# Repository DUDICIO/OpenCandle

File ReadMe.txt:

Open Candle Project

Smart desk lamp project

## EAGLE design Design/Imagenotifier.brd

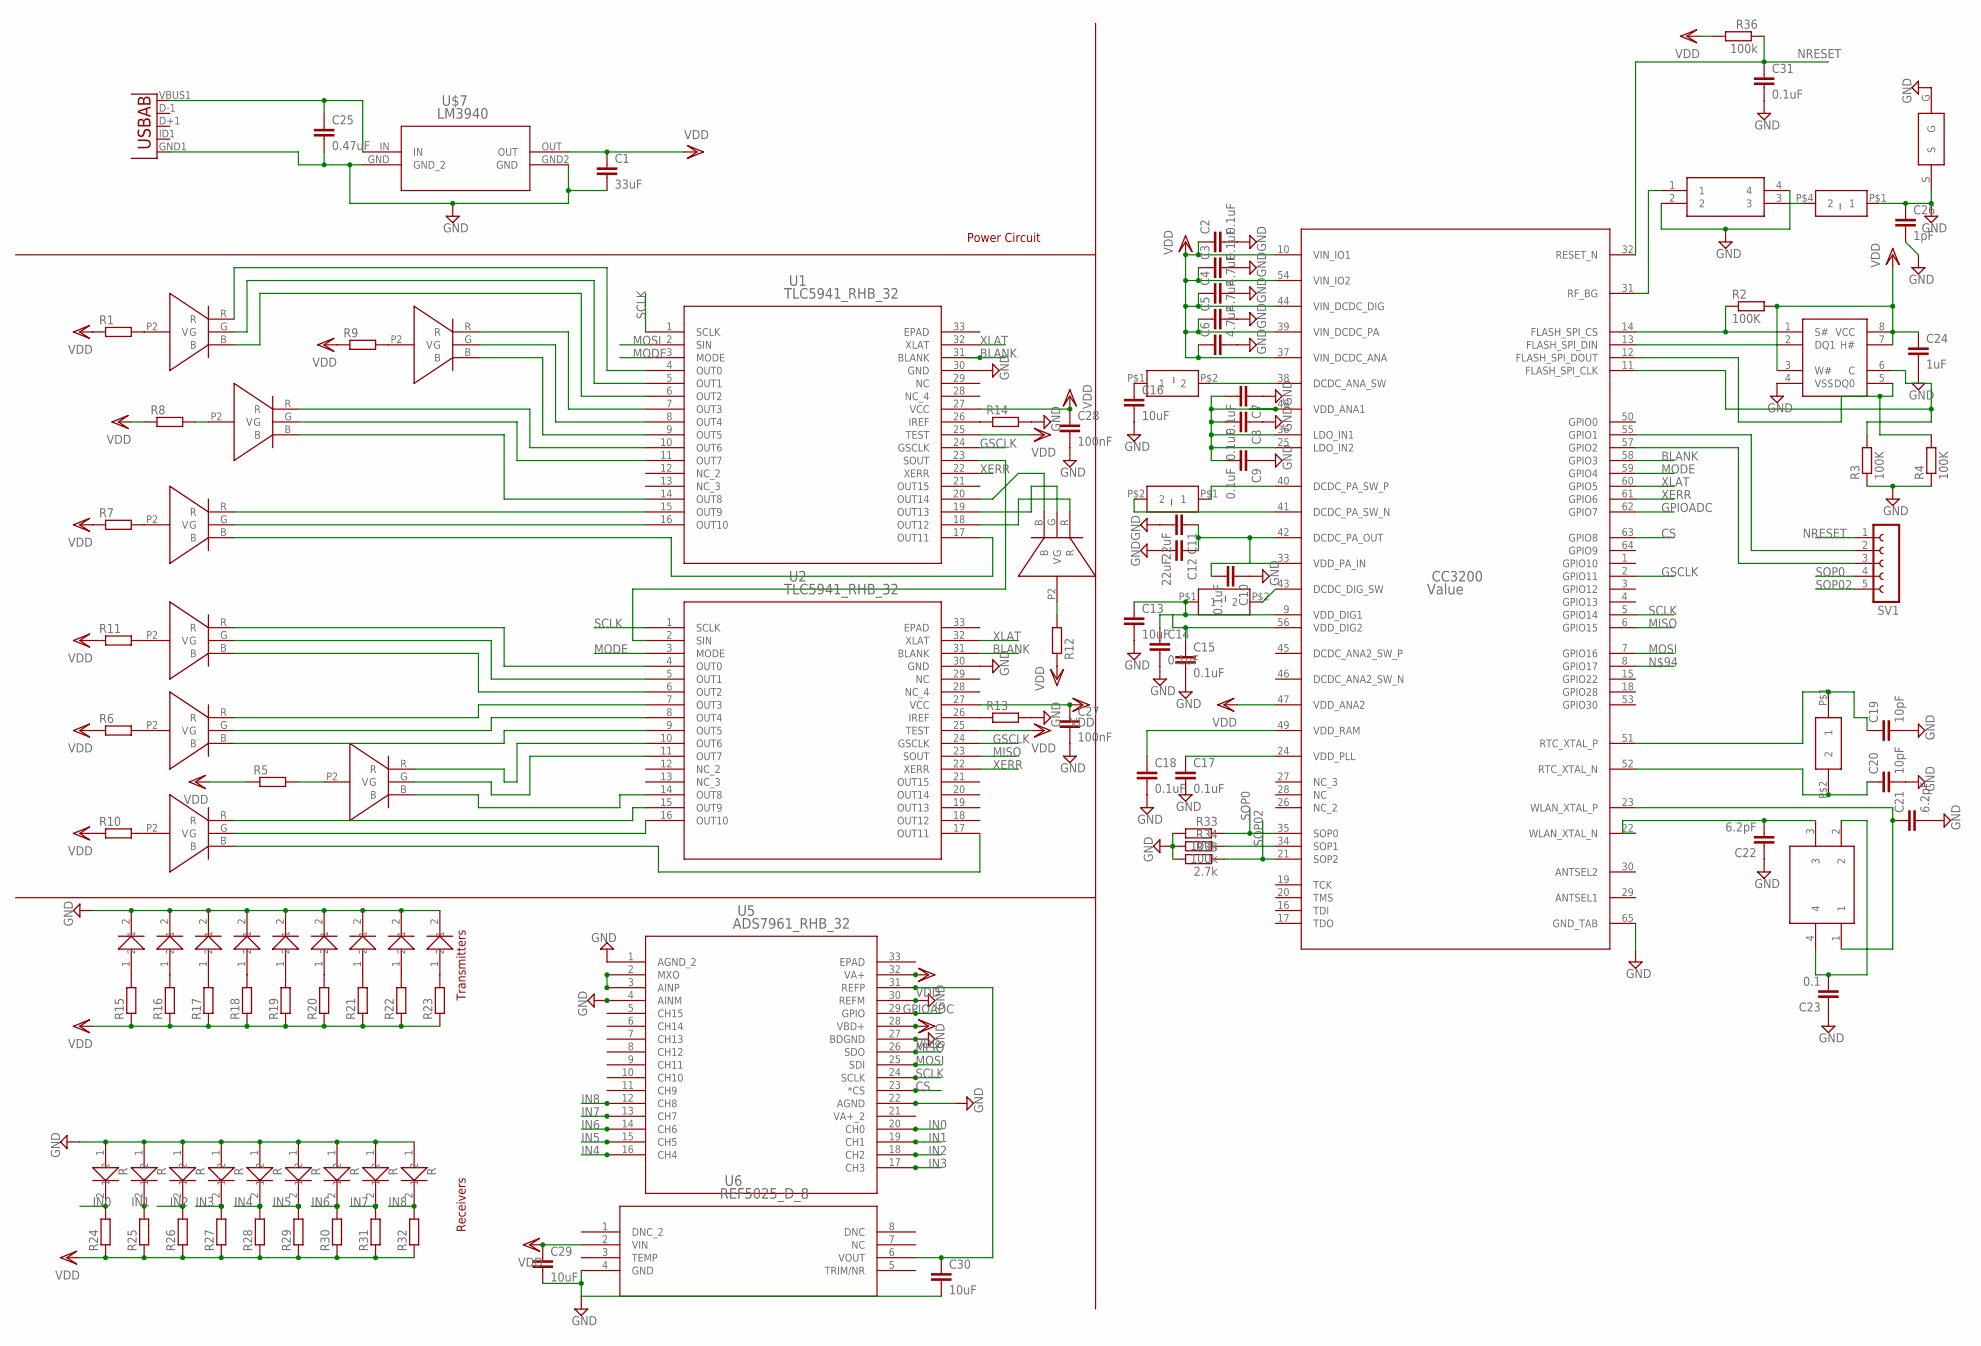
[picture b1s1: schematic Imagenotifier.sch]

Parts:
1: IRTRANS; IRTRANSCIEVER
C1: 33uF; C1206
C2, C3, C7, C8, C9, C10, C14, C15, C17, C18, C31: 0.1uF; 0805
C4, C5, C6: 4.7uF; 0805
C11, C12: 22uF; 0805
C13, C16, C29, C30: 10uF; 0805
C19, C20: 10pF; 0805
C21, C22: 6.2pF; 0805
C23: 0.1; 0805
C24: 1uF; 0805
C25: 0.47uF; C0805
C26: 1pF; 0805
C27, C28: 100nF; 0805
CC3200: Value; RGC0064A
CRYSTAL: ABS07-32.768KHZ-T
R1, R5, R6, R7, R8, R9, R10, R11, R12, R13, R14, R15, R16, R17, R18, R19, R20, R21, R22, R23, R24, R25, R26, R27, R28, R29, R30, R31, R32: R; R0805
R2, R3, R4: 100K; R0805
R33, R34, R36: 100k; R0805
R35: 2.7k; R0805
SV1: FE05-1
U1, U2: TLC5941_RHB_32; RHB32_3P15X3P15
U3: USB""; USB-MICRO-SMD
U5: ADS7961_RHB_32; RHB32_2P7X2P7
U6: REF5025_D_8; D8
U$1: IND1UH1008P; 1008IND2.2UH
U$2, U$3: IND2.6UH1008P; 1008IND2.2UH
U$5: Q24FA20H00396
U$6: FLASHM25PX80; SO08
U$7: LM3940; MP04A
U$8: DEA202450BT-1294C1-H
U$9: IND3.6NH402P; 0402INDUCTOR3.6NH
U$10: ANTENNAE-AH316M245001-T; ANTENNA-AH316M245001-T
U$11, U$12, U$13, U$14, U$15, U$16, U$17, U$18, U$19: RGBLED; 0.25WATT_RGB_THROUGH
U$20, U$22, U$23, U$24, U$25, U$26, U$27, U$28: IRTRANS; IRTRANSCIEVER
U$29, U$31, U$33, U$35, U$37, U$39, U$41, U$43, U$44: IRREC; IRREIVER

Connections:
BLANK: CC3200.58 (GPIO3), U1.31 (BLANK), U2.31 (BLANK)
CS: CC3200.63 (GPIO8), U5.23 (*CS)
EPAD: U5.33 (EPAD)
GND: 1.2, C1.2, C2.2, C3.2, C4.2, C5.2, C6.2, C7.1, C8.1, C9.1, C10.1, C11.2, C12.2, C13.2, C14.2, C15.2, C16.2, C18.2, C19.2, C20.2, C21.2, C22.1, C23.1, C24.2, C25.2, C26.1, C26.2, C27.2, C28.2, C29.2, C30.2, C31.2, CC3200.65 (GND_TAB), R3.1, R4.1, R13.2, R14.2, R33.2, R34.2, R35.2, U1.30 (GND), U2.30 (GND), U3.GND1 (GND), U5.4 (AINM), U5.22 (AGND), U5.27 (BDGND), U5.30 (REFM), U6.4 (GND), U$6.4 (VSS), U$7.GND (GND_2), U$7.GND2 (GND), U$8.2, U$8.4, U$9.P$1 (1), U$10.G, U$10.S, U$20.2, U$22.2, U$23.2, U$24.2, U$25.2, U$26.2, U$27.2, U$28.2, U$29.1, U$31.1, U$33.1, U$35.1, U$37.1, U$39.1, U$41.1, U$43.1, U$44.1
GPIOADC: CC3200.62 (GPIO7), U5.29 (GPIO)
GSCLK: CC3200.2 (GPIO11), U1.24 (GSCLK), U2.24 (GSCLK)
IN0: R24.2, U5.20 (CH0), U$29.2
IN1: R25.2, U5.19 (CH1), U$31.2
IN2: R26.2, U5.18 (CH2), U$33.2
IN3: R27.2, U5.17 (CH3), U$35.2
IN4: R28.2, U5.16 (CH4), U$37.2
IN5: R29.2, U5.15 (CH5), U$39.2
IN6: R30.2, U5.14 (CH6), U$41.2
IN7: R31.2, U5.13 (CH7), U$43.2
IN8: R32.2, U5.12 (CH8), U$44.2
MISO: CC3200.6 (GPIO15), U2.23 (SOUT), U5.26 (SDO)
MODE: CC3200.59 (GPIO4), U1.3 (MODE), U2.3 (MODE)
MOSI: CC3200.7 (GPIO16), U1.2 (SIN), U5.25 (SDI)
unnamed: C7.2, C8.2, C9.2, CC3200.25 (LDO_IN2), CC3200.36 (LDO_IN1), CC3200.48 (VDD_ANA1)
unnamed: CC3200.40 (DCDC_PA_SW_P), U$1.P$1 (1)
unnamed: CC3200.41 (DCDC_PA_SW_N), U$1.P$2 (2)
unnamed: C10.2, C11.1, C12.1, CC3200.33 (VDD_PA_IN), CC3200.42 (DCDC_PA_OUT)
unnamed: C13.1, C14.1, CC3200.9 (VDD_DIG1), U$3.P$1 (1)
unnamed: CC3200.43 (DCDC_DIG_SW), U$3.P$2 (2)
unnamed: C15.1, CC3200.56 (VDD_DIG2)
unnamed: CC3200.38 (DCDC_ANA_SW), U$2.P$2 (2)
unnamed: C16.1, U$2.P$1 (1)
unnamed: C18.1, CC3200.49 (VDD_RAM)
unnamed: C17.1, CC3200.24 (VDD_PLL)
unnamed: C19.1, CC3200.51 (RTC_XTAL_P), CRYSTAL.P$1 (1)
unnamed: C20.1, CC3200.52 (RTC_XTAL_N), CRYSTAL.P$2 (2)
unnamed: C21.1, CC3200.23 (WLAN_XTAL_P), U$5.1
unnamed: C22.2, CC3200.22 (WLAN_XTAL_N), U$5.3
unnamed: C23.2, U$5.2, U$5.4
unnamed: CC3200.14 (FLASH_SPI_CS), R2.1, U$6.1 (S#)
unnamed: CC3200.13 (FLASH_SPI_DIN), U$6.2 (DQ1)
unnamed: CC3200.11 (FLASH_SPI_CLK), R3.2, U$6.6 (C)
unnamed: C25.1, U3.VBUS1 (VBUS), U$7.IN
unnamed: CC3200.31 (RF_BG), U$8.1
unnamed: U$8.3, U$9.P$4 (2)
unnamed: R1.2, U$11.P2 (V)
unnamed: R5.2, U$14.P2 (V)
unnamed: R6.2, U$17.P2 (V)
unnamed: R7.2, U$12.P2 (V)
unnamed: R8.2, U$18.P2 (V)
unnamed: R9.2, U$15.P2 (V)
unnamed: R10.2, U$19.P2 (V)
unnamed: R11.2, U$16.P2 (V)
unnamed: R12.2, U$13.P2 (V)
unnamed: U1.4 (OUT0), U$11.R
unnamed: U1.5 (OUT1), U$11.G
unnamed: U1.6 (OUT2), U$11.B
unnamed: U1.7 (OUT3), U$15.R
unnamed: U1.8 (OUT4), U$15.G
unnamed: U1.9 (OUT5), U$15.B
unnamed: U1.10 (OUT6), U$18.R
unnamed: U1.11 (OUT7), U$18.G
unnamed: U1.14 (OUT8), U$18.B
unnamed: U1.15 (OUT9), U$12.R
unnamed: U1.16 (OUT10), U$12.G
unnamed: U1.17 (OUT11), U$12.B
unnamed: U1.18 (OUT12), U$13.R
unnamed: U1.19 (OUT13), U$13.G
unnamed: U1.20 (OUT14), U$13.B
unnamed: U2.4 (OUT0), U$16.R
unnamed: U2.5 (OUT1), U$16.G
unnamed: U2.6 (OUT2), U$16.B
unnamed: U2.7 (OUT3), U$17.R
unnamed: U2.9 (OUT5), U$17.B
unnamed: U2.10 (OUT6), U$14.R
unnamed: U2.8 (OUT4), U$17.G
unnamed: U2.11 (OUT7), U$14.G
unnamed: U2.14 (OUT8), U$14.B
unnamed: U5.2 (MXO), U5.3 (AINP)
unnamed: U2.15 (OUT9), U$19.R
unnamed: U2.16 (OUT10), U$19.G
unnamed: U2.17 (OUT11), U$19.B
unnamed: U1.23 (SOUT), U2.2 (SIN)
unnamed: 1.1, R15.2
unnamed: R14.1, U1.26 (IREF)
unnamed: R16.2, U$22.1
unnamed: R13.1, U2.26 (IREF)
unnamed: C30.1, U5.31 (REFP), U6.6 (VOUT)
unnamed: CC3200.34 (SOP1), R34.1
unnamed: CC3200.55 (GPIO1), SV1.2
unnamed: CC3200.57 (GPIO2), SV1.3
unnamed: R17.2, U$23.1
unnamed: R18.2, U$24.1
unnamed: R19.2, U$25.1
unnamed: R20.2, U$26.1
unnamed: R21.2, U$27.1
unnamed: R22.2, U$28.1
unnamed: R23.2, U$20.1
unnamed: CC3200.12 (FLASH_SPI_DOUT), R4.2, U$6.5 (DQ0)
NRESET: C31.1, CC3200.32 (RESET_N), R36.1, SV1.1
SCLK: CC3200.5 (GPIO14), U1.1 (SCLK), U2.1 (SCLK), U5.24 (SCLK)
SOP0: CC3200.35 (SOP0), R33.1, SV1.4
SOP02: CC3200.21 (SOP2), R35.1, SV1.5
VA+_2: U5.21 (VA+_2)
VDD: C1.1, C2.1, C3.1, C4.1, C5.1, C6.1, C24.1, C27.1, C28.1, C29.1, CC3200.10 (VIN_IO1), CC3200.37 (VIN_DCDC_ANA), CC3200.39 (VIN_DCDC_PA), CC3200.44 (VIN_DCDC_DIG), CC3200.47 (VDD_ANA2), CC3200.54 (VIN_IO2), R1.1, R2.2, R5.1, R6.1, R7.1, R8.1, R9.1, R10.1, R11.1, R12.1, R15.1, R16.1, R17.1, R18.1, R19.1, R20.1, R21.1, R22.1, R23.1, R24.1, R25.1, R26.1, R27.1, R28.1, R29.1, R30.1, R31.1, R32.1, R36.2, U1.25 (TEST), U1.27 (VCC), U2.25 (TEST), U2.27 (VCC), U5.28 (VBD+), U5.32 (VA+), U6.2 (VIN), U$6.3 (W#), U$6.7 (H#), U$6.8 (VCC), U$7.OUT
XERR: CC3200.61 (GPIO6), U1.22 (XERR), U2.22 (XERR)
XLAT: CC3200.60 (GPIO5), U1.32 (XLAT), U2.32 (XLAT)

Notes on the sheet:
Power Circuit
Transmitters
Receivers

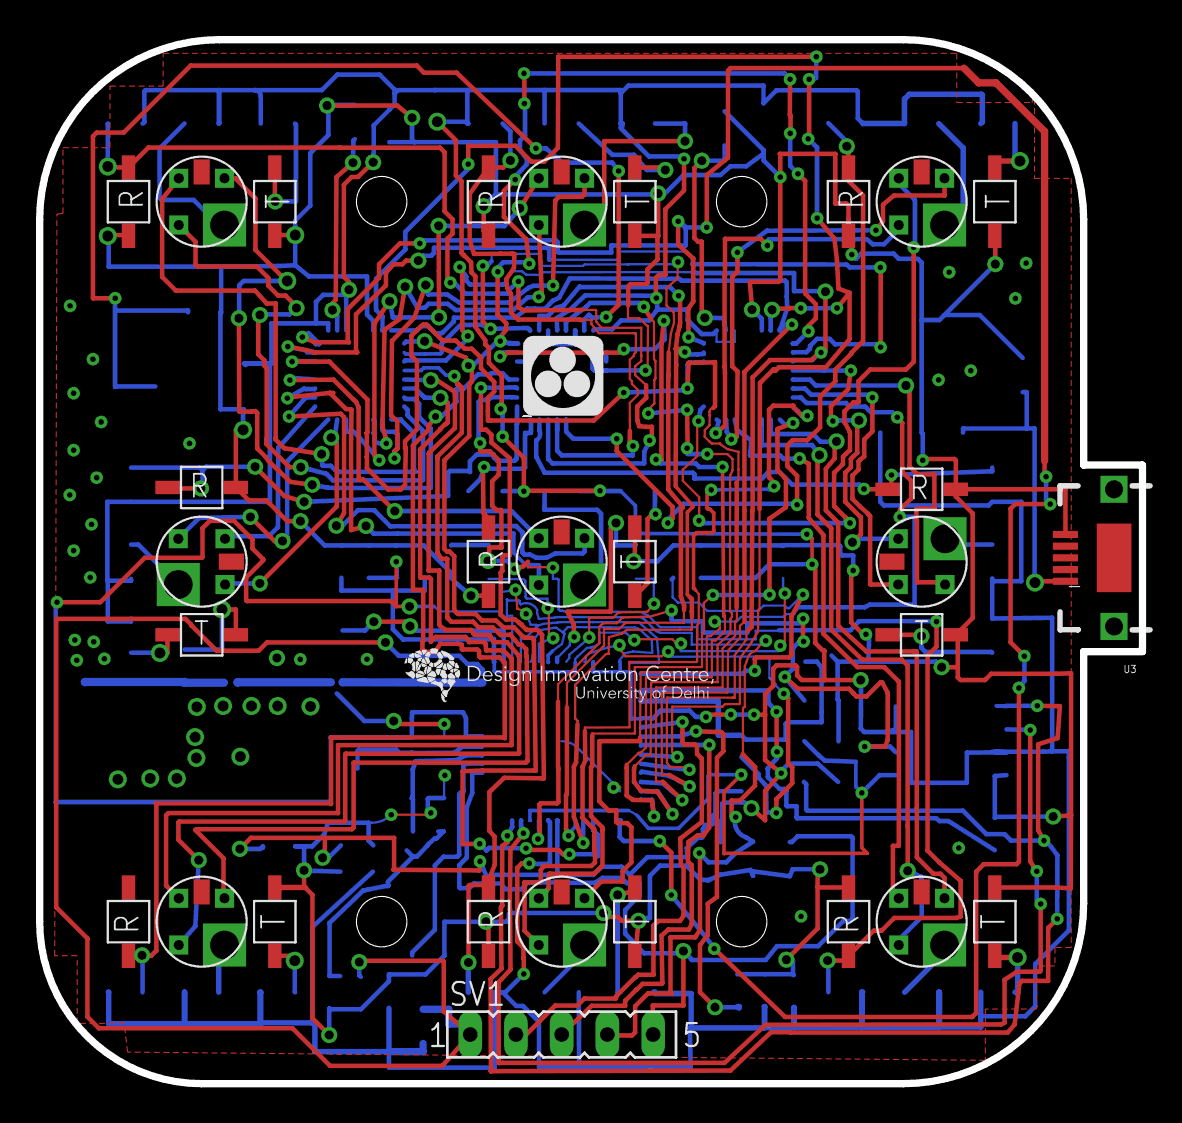
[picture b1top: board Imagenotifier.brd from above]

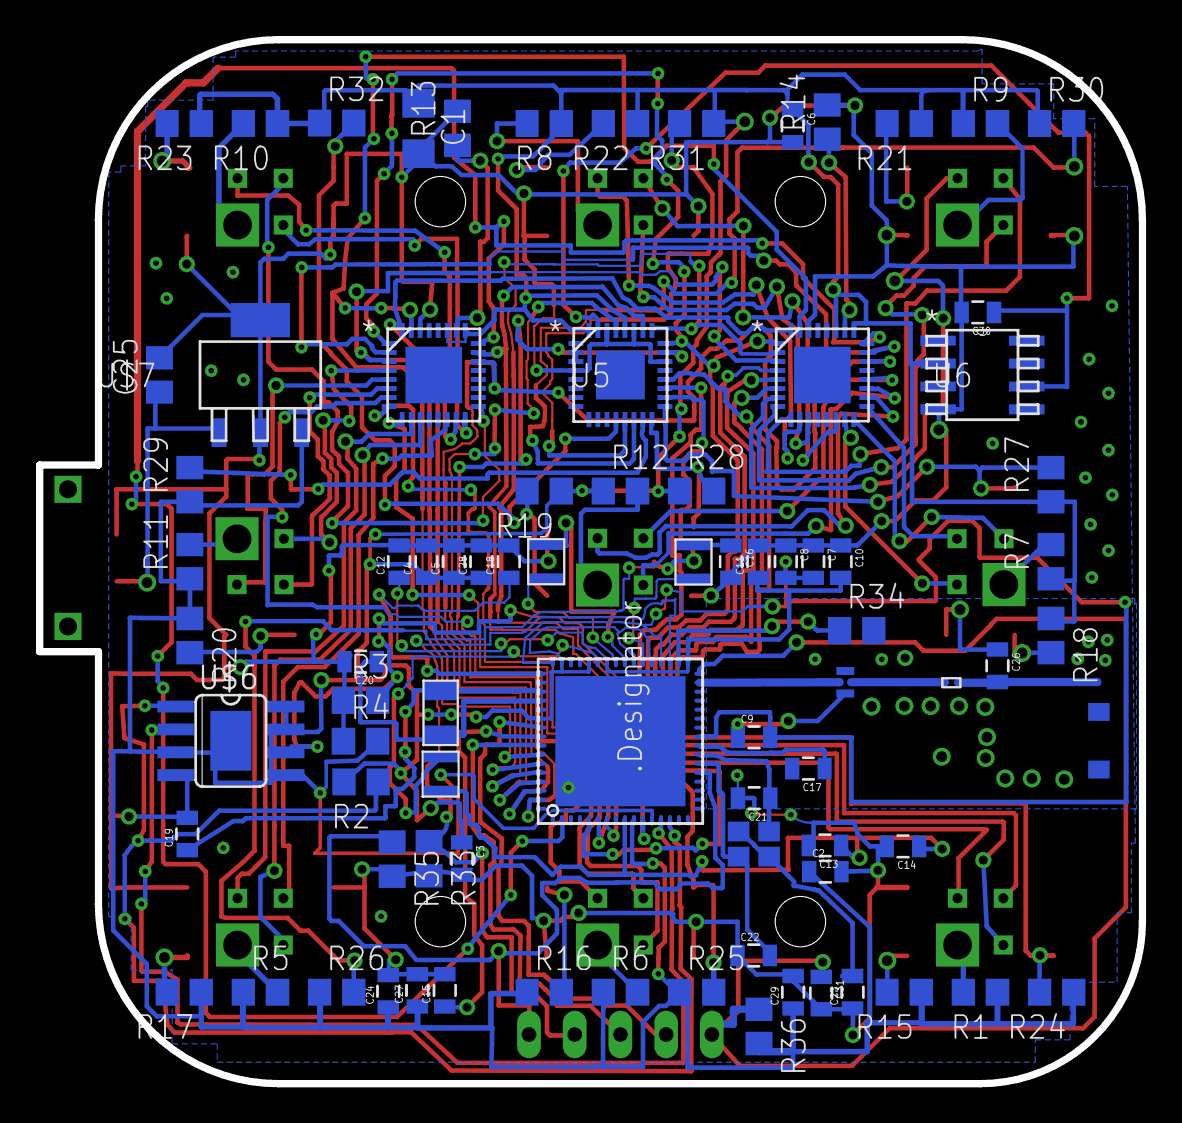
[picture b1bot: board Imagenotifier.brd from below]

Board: 2 copper layers, 61.3 x 58.0 mm, 111 parts (82 on the bottom side), 100 nets.

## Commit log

2017-02-21 Added readme
2017-02-21 Version 0.1 Electronic Boards Added
2017-03-05 Testing

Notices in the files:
parts and their libraries:
SparkFun-Capacitors: Licensing: Creative Commons ShareAlike 4.0 International - https://creativecommons.org/licenses/by-sa/4.0
